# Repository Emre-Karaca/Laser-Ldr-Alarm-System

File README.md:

# Laser-Ldr-Alarm-System
This low-cost security system uses a laser and Light-Dependent Resistor (LDR) to detect door openings and trigger alarms. The signal is processed via a comparator and 555 Timer IC to trigger a buzzer and LED for audible and visual alerts. It’s designed to provide simple, reliable, and affordable home security, especially for vulnerable groups like elderly individuals living alone.

## Working Principle:
The laser shines on the LDR, keeping the system passive. When the door opens, the laser beam is interrupted, causing the LDR’s resistance to change. This triggers a comparator, activating a 555 Timer IC to sound an alarm (buzzer) and light an LED.

## Components:
Laser: Illuminates the LDR and keeps the system passive.
LDR: Detects changes in light intensity when the laser is interrupted.
Comparator: Compares the LDR’s signal to a reference voltage.
555 Timer: Triggers the alarm system when activated. It works in astable configuration.
Alarm (Buzzer + LED): Provides audible and visual alerts.

## Circuit Overview:
When the laser beam is interrupted, the LDR’s resistance increases, altering the comparator’s output. This activates the 555 Timer, producing a signal that drives the buzzer and LED.

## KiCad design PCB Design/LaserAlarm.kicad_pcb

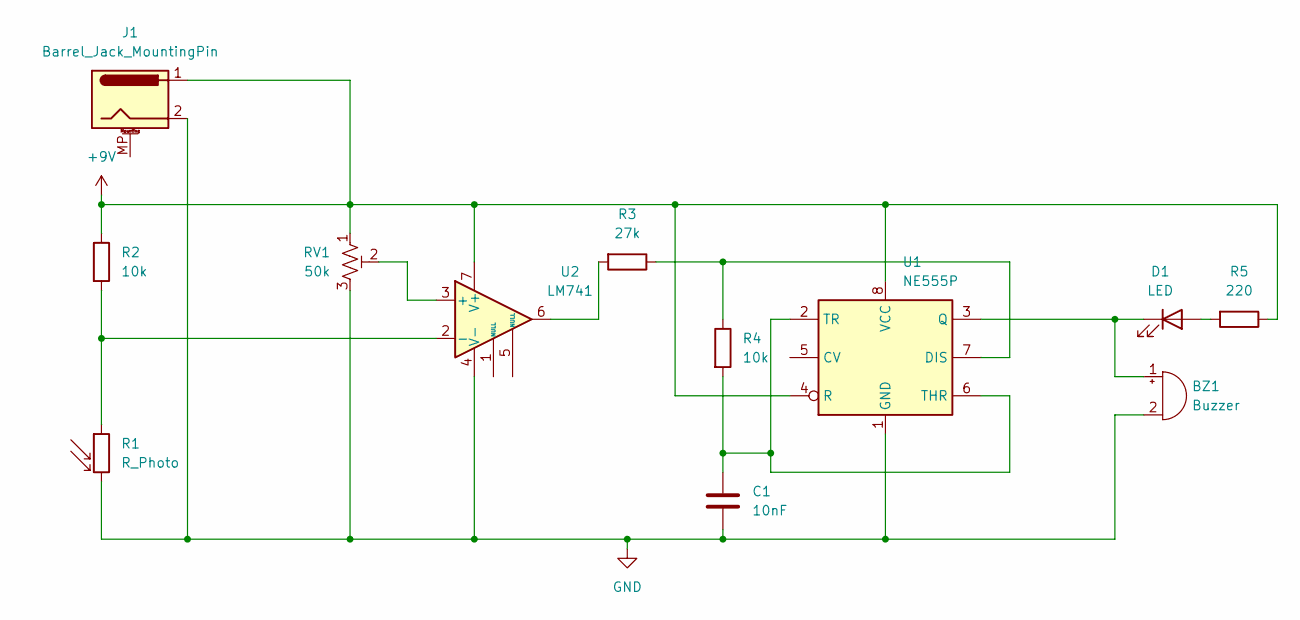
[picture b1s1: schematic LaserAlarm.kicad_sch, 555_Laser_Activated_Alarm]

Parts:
BZ1: Buzzer; Buzzer_12x9.5RM7.6
C1: 10nF; C_Axial_L5.1mm_D3.1mm_P7.50mm_Horizontal
D1: LED; LED_D5.0mm_Horizontal_O1.27mm_Z3.0mm
J1: Barrel_Jack_MountingPin; BarrelJack_Kycon_KLDX-0202-xC_Horizontal
R1: R_Photo; R_LDR_5.1x4.3mm_P3.4mm_Vertical
R2, R4: 10k; R_Axial_DIN0204_L3.6mm_D1.6mm_P5.08mm_Horizontal
R3: 27k; R_Axial_DIN0204_L3.6mm_D1.6mm_P5.08mm_Horizontal
R5: 220; R_Axial_DIN0204_L3.6mm_D1.6mm_P5.08mm_Horizontal
RV1: 50k; Potentiometer_Bourns_3269W_Vertical
U1: NE555P; DIP-8_W7.62mm
U2: LM741; DIP-8_W7.62mm

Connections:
+9V: J1.1, R2.1, R5.1, RV1.1, U1.4 (R), U1.8 (VCC), U2.7 (V+)
GND: BZ1.2 (-), C1.2, J1.2, R1.2, RV1.3, U1.1 (GND), U2.4 (V-)
unnamed: BZ1.1 (+), D1.1 (K), U1.3 (Q)
unnamed: D1.2 (A), R5.2
unnamed: R3.2, U2.6
unnamed: R3.1, R4.1, U1.7 (DIS)
unnamed: C1.1, R4.2, U1.2 (TR), U1.6 (THR)
unnamed: RV1.2, U2.3 (+)
unnamed: R1.1, R2.2, U2.2 (-)

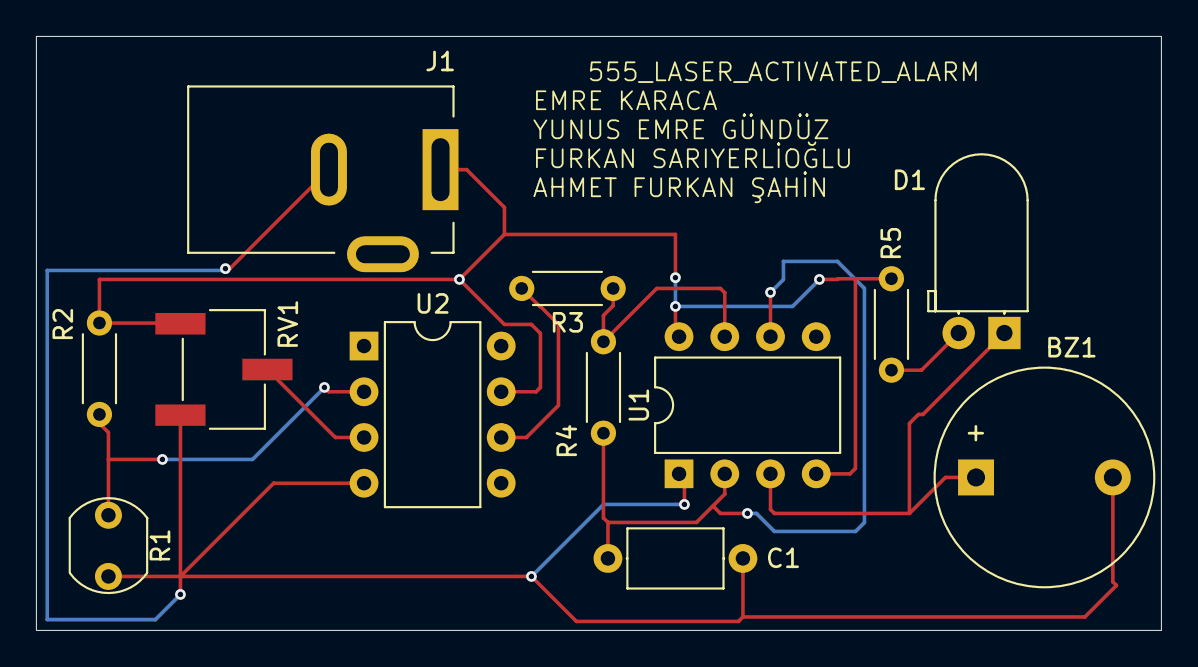
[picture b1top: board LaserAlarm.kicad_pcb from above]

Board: 2 copper layers, 62.5 x 33.0 mm, 12 parts (0 on the bottom side), 9 nets.

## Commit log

2025-01-25 Rename image.png to CircuitDiagram.png
2025-01-25 Rename project_block_diagram.pdf to block_diagram.pdf
2025-01-25 Rename CircuitDiagram.png to circuit_diagram.png
2025-01-25 Rename Project_report.pdf to project_report.pdf
